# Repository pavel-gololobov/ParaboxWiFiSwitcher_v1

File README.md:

# ParaboxWiFiSwitcher_v1
Parabox Wi-Fi Switcher

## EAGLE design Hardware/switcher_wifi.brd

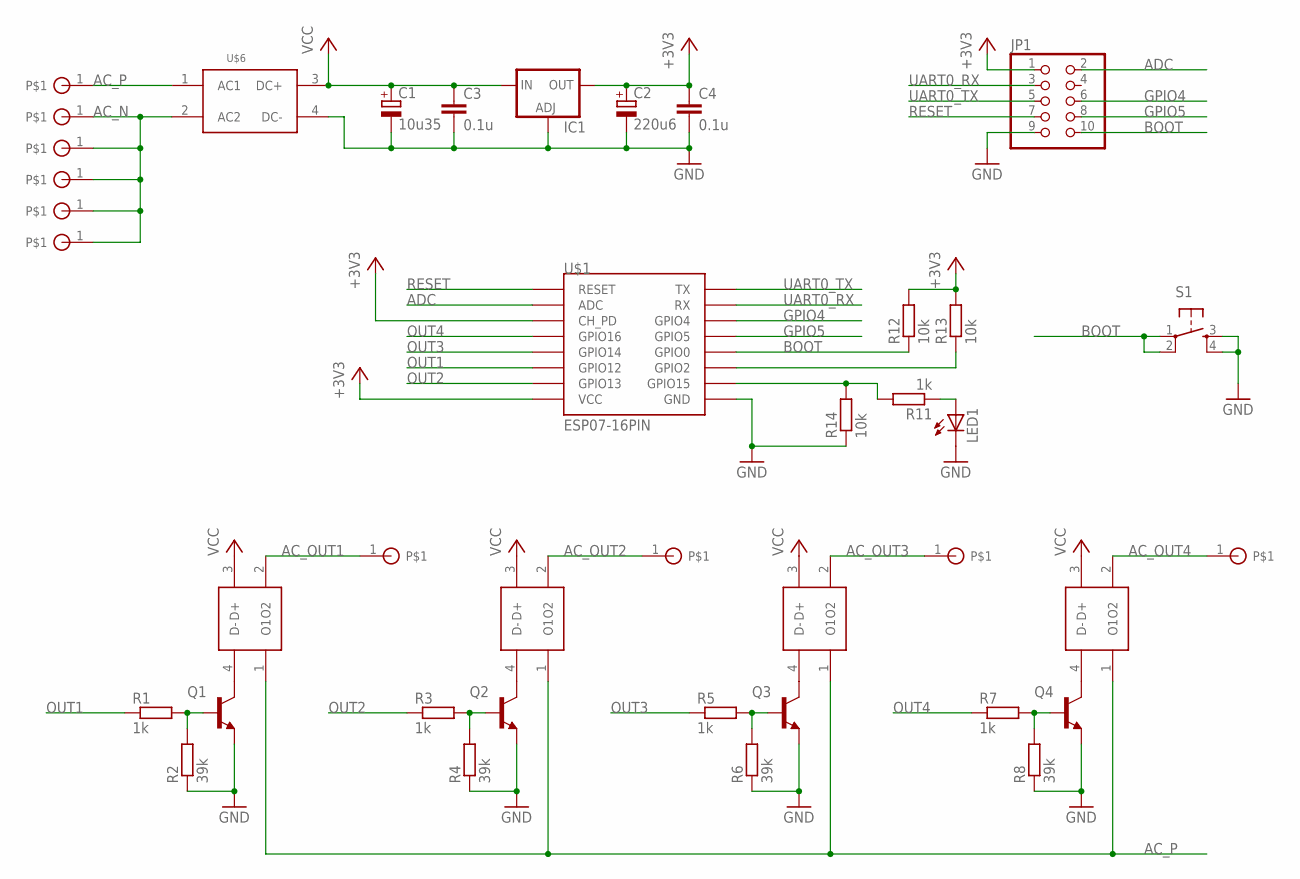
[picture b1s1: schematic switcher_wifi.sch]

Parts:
C1: 10u35; SMC_D
C2: 220u6; SMC_D
C3, C4: 0.1u; C0805
IC1: LD117ADT33TR; DPACK
JP1: PINHD-2X5; 2X05
LED1: LED3MM
Q1, Q2, Q3, Q4: BC817-16SMD; SOT23-BEC
R1, R3, R5, R7, R11: 1k; M0805
R2, R4, R6, R8: 39k; M0805
R12, R13, R14: 10k; M0805
S1: TAC_SWITCHPTH; TACTILE-PTH
U$1: ESP07-16PIN
U$2, U$3, U$4, U$5: G3MB-202P
U$6: AC-DC-5V-ALI1; AC-DC-ALI1
U$8, U$9, U$10, U$11, U$12, U$13, U$14, U$15, U$16, U$17: PWR_PIN

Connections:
+3V3: C2.+, C4.1, IC1.4 (OUT), JP1.1, R12.2, R13.2, U$1.CH_PD, U$1.VCC
AC_N: U$6.2 (AC2), U$9.1, U$14.1, U$15.1, U$16.1, U$17.1
AC_OUT1: U$2.2 (O2), U$10.1
AC_OUT2: U$3.2 (O2), U$11.1
AC_OUT3: U$4.2 (O2), U$12.1
AC_OUT4: U$5.2 (O2), U$13.1
AC_P: U$2.1 (O1), U$3.1 (O1), U$4.1 (O1), U$5.1 (O1), U$6.1 (AC1), U$8.1
ADC: JP1.2, U$1.ADC
BOOT: JP1.10, R12.1, S1.1, S1.2, U$1.GPIO0
GND: C1.-, C2.-, C3.2, C4.2, IC1.1 (ADJ), JP1.9, LED1.K (C), Q1.E, Q2.E, Q3.E, Q4.E, R2.1, R4.1, R6.1, R8.1, R14.1, S1.3, S1.4, U$1.GND, U$6.4 (DC-)
GPIO4: JP1.6, U$1.GPIO4
GPIO5: JP1.8, U$1.GPIO5
unnamed: Q1.C, U$2.4 (D-)
unnamed: Q1.B, R1.2, R2.2
unnamed: Q2.C, U$3.4 (D-)
unnamed: LED1.A, R11.1
unnamed: Q2.B, R3.2, R4.2
unnamed: Q3.C, U$4.4 (D-)
unnamed: Q3.B, R5.2, R6.2
unnamed: Q4.C, U$5.4 (D-)
unnamed: Q4.B, R7.2, R8.2
unnamed: R13.1, U$1.GPIO2
unnamed: R11.2, R14.2, U$1.GPIO15
OUT1: R1.1, U$1.GPIO12
OUT2: R3.1, U$1.GPIO13
OUT3: R5.1, U$1.GPIO14
OUT4: R7.1, U$1.GPIO16
RESET: JP1.7, U$1.REST (RESET)
UART0_RX: JP1.3, U$1.RX
UART0_TX: JP1.5, U$1.TX
VCC: C1.+, C3.1, IC1.3 (IN), U$2.3 (D+), U$3.3 (D+), U$4.3 (D+), U$5.3 (D+), U$6.3 (DC+)

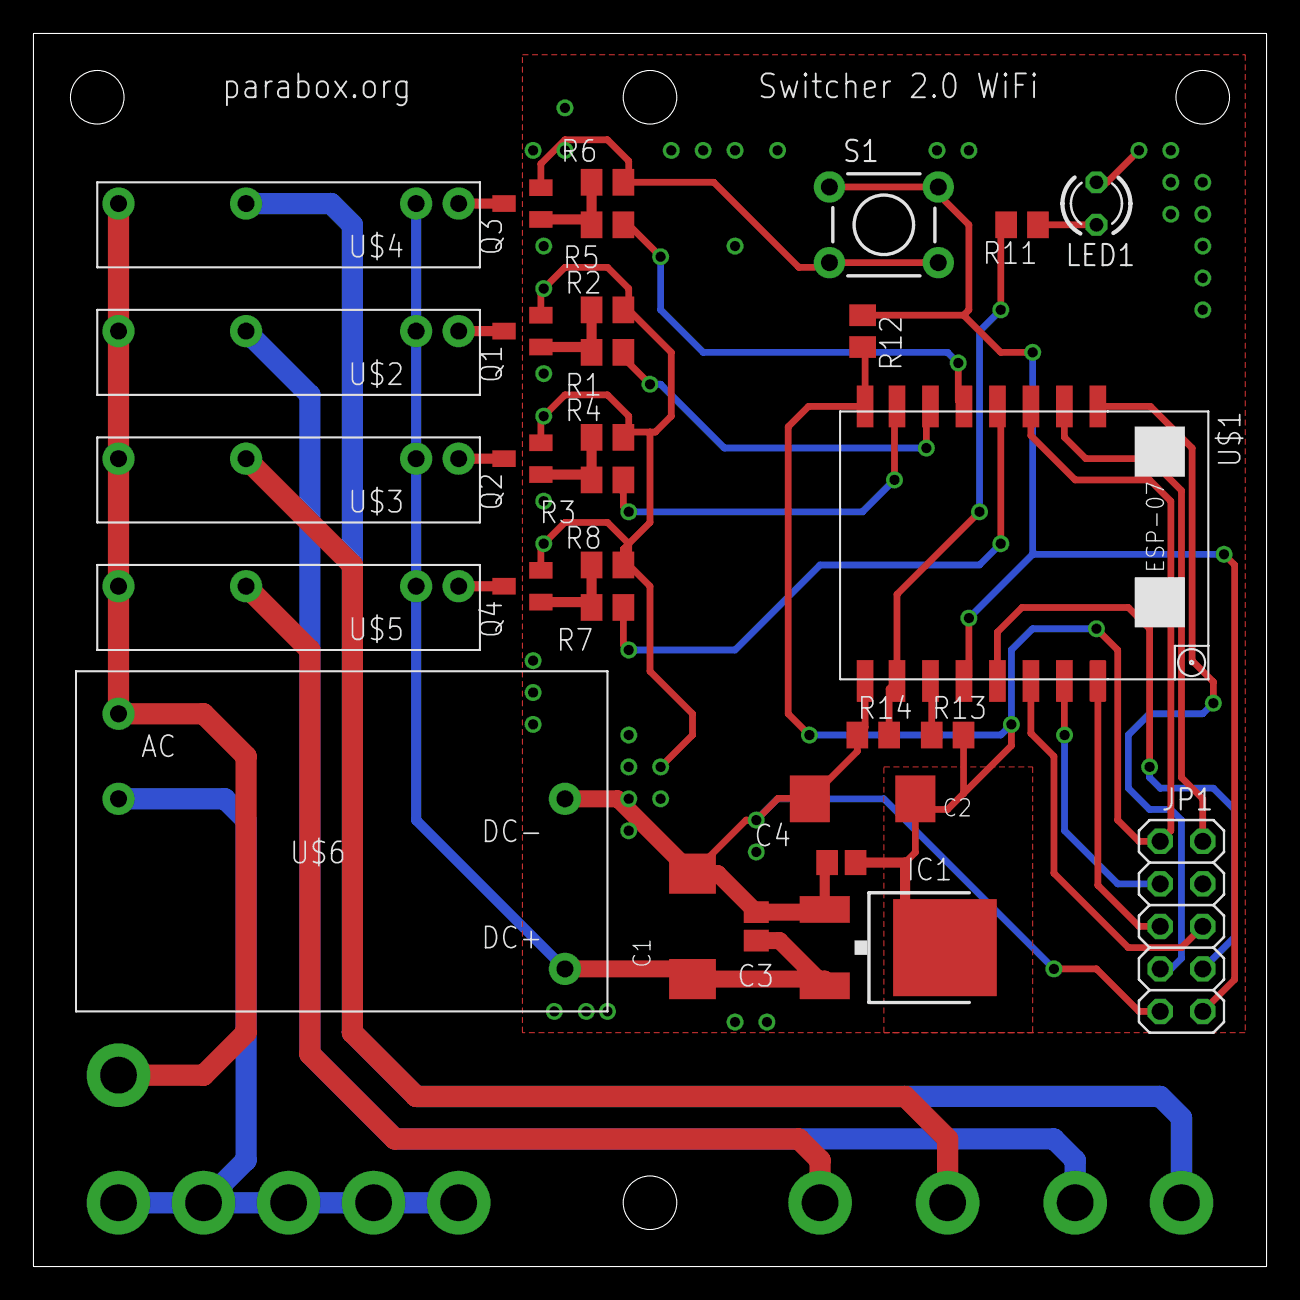
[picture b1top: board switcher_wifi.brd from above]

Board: 2 copper layers, 73.7 x 73.7 mm, 40 parts (0 on the bottom side), 31 nets.

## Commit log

2018-02-03 First beta version
